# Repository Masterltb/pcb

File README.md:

# FreshVend — PCB điều khiển máy bán tô trái cây

**Rev-S3 là bản mẫu đang phát triển trên nhánh `fix/revs3-min-drill-0p3`.** Dùng ESP32-S3-WROOM-1U-N8, anten IPEX, USB-C dữ liệu và hai buck servo 6 V gá ngoài. RevB ở dưới là bản lịch sử; chưa bản nào được nghiệm thu sản xuất hàng loạt.

## Bàn giao Rev-S3

- [Bắt đầu tại đây: trạng thái, sơ đồ thư mục, bản hiện hành và backup](docs/rev_s3/handoff/README.md)
- [Project KiCad 10 Rev-S3](hardware/rev_s3/FV-CTRL_RevS3.kicad_pro)
- [Gerber 0,30 mm hiện hành cho 5 mẫu](releases/rev_s3/prototype-0p3-2026-10-29/FV-CTRL_RevS3-prototype-0p3-2026-10-29-Gerber.zip)
- [BOM nháp để kiểm tra linh kiện JLCPCB](assembly/rev_s3/draft/RevS3-JLCPCB-BOM-MATCHING-DRAFT.csv) và [CPL nháp](assembly/rev_s3/draft/RevS3-JLCPCB-CPL-MATCHING-DRAFT.csv)
- [ERC/DRC/parity hiện hành](reports/rev_s3/verified/RevS3-final-drc.json) và [rủi ro đặt hàng](docs/rev_s3/RevS3-JLCPCB-order-readiness-2026-10-29.md)

Các vị trí J4, J11/J12, J21 đang thiếu hàng ở báo giá JLCPCB; F2/F3 chưa có mã linh kiện. Gói Gerber dùng để kiểm tra/đặt mẫu PCB, chưa phải chứng nhận PCBA hoàn chỉnh.

## Bản RevB lưu để tham khảo

- [Project KiCad 10 RevB](hardware/revb/FV-CTRL_RevB.kicad_pro)
- [Trạng thái, kết quả kiểm tra và rủi ro cần duyệt](docs/revb/RevB-status.md)
- [ZIP review giữ nguyên thư mục](releases/revb/FV-CTRL_RevB-review.zip)
- [Gerber + drill mẫu RevB, 2026-10-26](releases/revb/FV-CTRL_RevB-Gerber-2026-10-26.zip)
- [Gói gửi xưởng báo giá/mẫu: Gerber, BOM, CPL và DFM](releases/revb/FV-CTRL_RevB-Prototype-Handoff-2026-10-26.zip)
- [Ghi chú lần xuất Gerber và giới hạn nghiệm thu](docs/revb/RevB-prototype-export-2026-10-26.md)
- [BOM linh kiện](docs/revb/bom/FV-CTRL_RevB-bom-review.csv)
- [Checklist cấp nguồn và chạy mẫu](docs/revb/RevB-review-and-bringup.md)
- [Mô phỏng Wokwi: ESP32, servo, IR và server local](simulation/revb/README.md)

Đọc [PROJECT.md](PROJECT.md) về yêu cầu và [AGENTS.md](AGENTS.md) trước khi sửa thiết kế. Không dùng các bản RevA/RevA2 để thay cho RevB.

## Cấu trúc

```text
hardware/
  rev_s3/               Project Rev-S3 đang phát triển; schematic, PCB và bảng thư viện
  revb/                 Project RevB lịch sử: mainboard, schematic và bảng thư viện
  reva2/                Bản cũ tham khảo: mainboard và IR RX
  archive/reva/         Nguồn RevA lịch sử, gồm các sửa đổi cục bộ chưa commit
libs/                   Thư viện dùng chung, giữ nguyên tên thư viện
cad/                    Cơ khí và mô phỏng FreeCAD
simulation/revb/        Mô phỏng chức năng Wokwi; không phải firmware production

docs/
  rev_s3/handoff/       Điểm vào bàn giao, đặt hàng và bring-up bản mẫu
  rev_s3/               Review, PDF schematic, STEP, pinout Rev-S3
  revb/
    bom/                BOM tổng, BOM SMT báo giá, linh kiện THT
    assembly/           Hình lắp ráp, ảnh 3D minh họa, tọa độ SMT, bản đồ via EP
    schematic/          Schematic xuất SVG/PNG để đọc
    RevB-status.md      Bắt đầu review tại đây
  reva2/                Tài liệu bản cũ
  archive/reva/         Tài liệu RevA lịch sử
  references/           Datasheet và hình tham khảo
  project/              Yêu cầu chung và ghi chú thử nghiệm
  mechanical/           Báo cáo cơ khí

reports/
  rev_s3/verified/      ERC, DRC/parity và netlist hiện hành
  rev_s3/work/          Log/checkpoint thử nghiệm cục bộ; không đưa vào Git
  revb/verified/        ERC/DRC, netlist và kết quả kiểm tra hiện hành
  revb/history/         Báo cáo trung gian đã lưu trong Git
  revb/work/            File chạy tạm/autoroute cục bộ, không đưa vào Git
  reva2/                Báo cáo RevA2
  archive/reva/         Báo cáo RevA lịch sử
  local/                Dữ liệu phân tích cục bộ, không đưa vào Git

releases/
  rev_s3/               Gerber hiện hành và các ZIP backup có ngày
  revb/                 ZIP review, Gerber/handoff mẫu có ngày và manifest SHA256
  archive/              ZIP/Gerber/handover các bản cũ; không dùng đặt RevB

tools/                  Công cụ; xem tools/README.md trước khi chạy
tests/                 Các bài kiểm tra generator RevA lịch sử
```

Các thư mục `hardware/<revision>` phải giữ quan hệ với `libs/`; không kéo riêng file project sang nơi khác. Trước khi đặt Rev-S3, đọc [bàn giao Rev-S3](docs/rev_s3/handoff/README.md) để phân biệt gói hiện hành với backup. Chưa có nghiệm thu phần cứng hoặc chấp thuận DFM của xưởng.

Xem [quy ước sắp xếp và kiểm tra](docs/repository-layout.md) để biết cách thêm file đúng chỗ.

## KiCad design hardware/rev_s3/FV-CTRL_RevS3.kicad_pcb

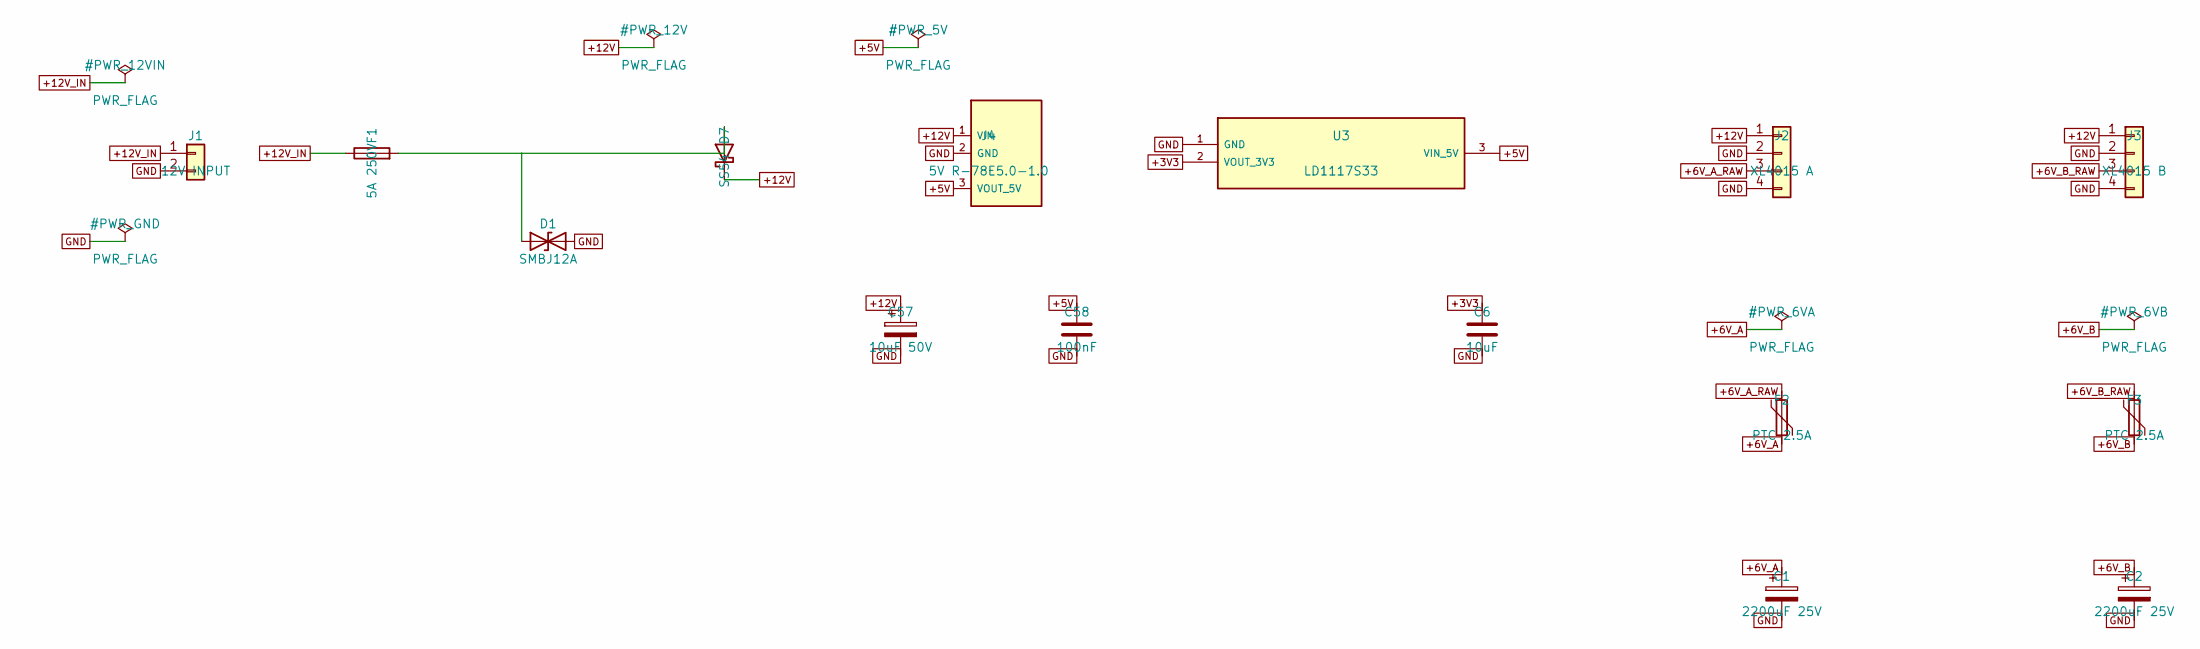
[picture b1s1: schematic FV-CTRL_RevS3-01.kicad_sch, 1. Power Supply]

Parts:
C1, C2: 2200uF 25V; CP_Radial_D12.5mm_P5.00mm
C6: 10uF; C_0603_1608Metric
C57: 10uF 50V; CP_Radial_D5.0mm_P2.00mm
C58: 100nF; C_0603_1608Metric
D1: SMBJ12A; D_SMB
D7: SS54; D_SMC
F1: 5A 250V; Fuseholder_Cylinder-5x20mm_Schurter_0031_8201_Horizontal_Op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
F2, F3: PTC 2.5A; Fuse_Bourns_MF-RHT300
J1: 12V INPUT; PhoenixContact_MSTBA_2,5_2-G-5,08_1x02_P5.08mm_Horizontal
J2: XL4015 A; PhoenixContact_MSTBA_2,5_4-G-5,08_1x04_P5.08mm_Horizontal
J3: XL4015 B; PhoenixContact_MSTBA_2,5_4-G-5,08_1x04_P5.08mm_Horizontal
J4: 5V R-78E5.0-1.0; RECOM_R78E5V1A
U3: LD1117S33; SOT-223-3_TabPin2

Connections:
+3V3: C6.1, U3.2 (VOUT_3V3); also elsewhere on the board
+6V_A_RAW: F2.1, J2.3
+6V_B_RAW: F3.1, J3.3
unnamed: D1.1 (A1), D7.2 (A), F1.2

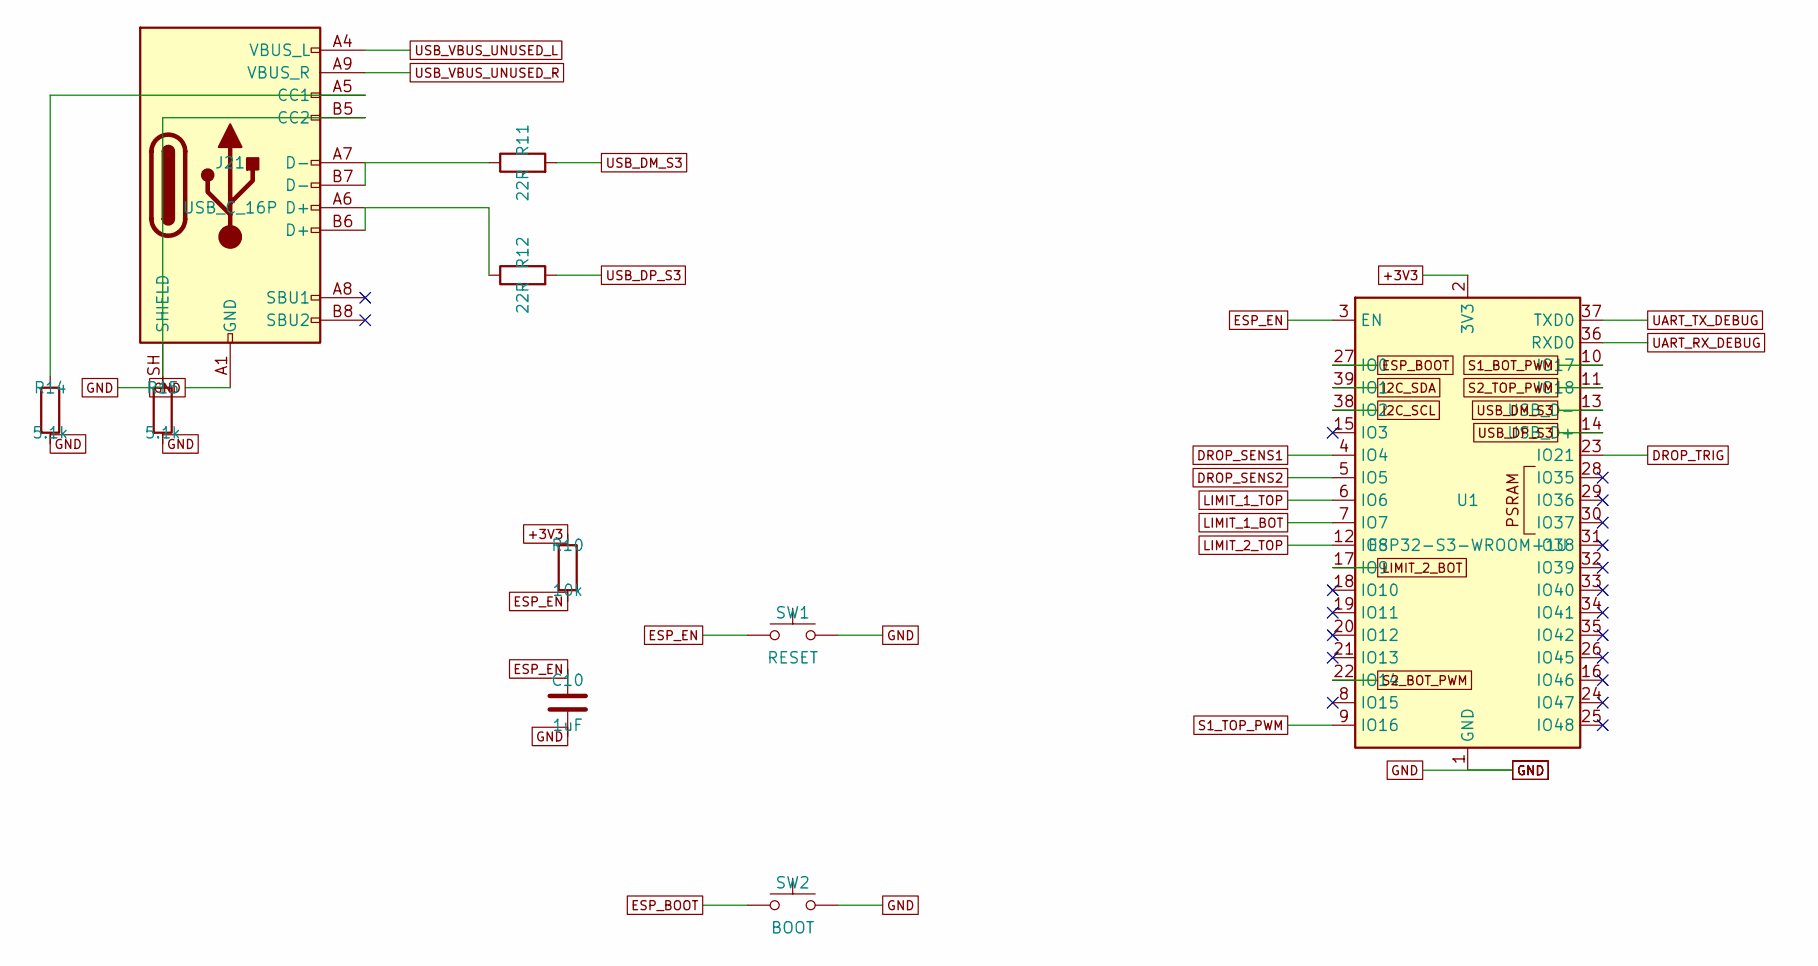
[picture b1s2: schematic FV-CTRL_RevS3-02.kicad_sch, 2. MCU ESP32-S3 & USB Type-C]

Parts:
C10: 1uF; C_0603_1608Metric
J21: USB_C_16P; USB_C_Receptacle_GCT_USB4105-xx-A_16P_TopMnt_Horizontal
R10: 10k; R_0603_1608Metric
R11, R12: 22R; R_0603_1608Metric
R14, R15: 5.1k; R_0603_1608Metric
SW1: RESET; SW_Push_SPST_NO_Alps_SKRK
SW2: BOOT; SW_Push_SPST_NO_Alps_SKRK
U1: ESP32-S3-WROOM-1U; ESP32-S3-WROOM-1U_0p3

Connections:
+3V3: R10.1, U1.2 (3V3); also elsewhere on the board
DROP_SENS1: U1.4 (IO4); also elsewhere on the board
DROP_SENS2: U1.5 (IO5); also elsewhere on the board
DROP_TRIG: U1.23 (IO21); also elsewhere on the board
ESP_BOOT: SW2.1, U1.27 (IO0)
ESP_EN: C10.1, R10.2, SW1.1, U1.3 (EN)
I2C_SCL: U1.38 (IO2); also elsewhere on the board
I2C_SDA: U1.39 (IO1); also elsewhere on the board
LIMIT_1_BOT: U1.7 (IO7); also elsewhere on the board
LIMIT_1_TOP: U1.6 (IO6); also elsewhere on the board
LIMIT_2_BOT: U1.17 (IO9); also elsewhere on the board
LIMIT_2_TOP: U1.12 (IO8); also elsewhere on the board
unnamed: J21.A5 (CC1), R14.1
unnamed: J21.B5 (CC2), R15.1
unnamed: J21.A6 (D+), J21.B6 (D+), R12.1
unnamed: J21.A7 (D-), J21.B7 (D-), R11.1
S1_BOT_PWM: U1.10 (IO17); also elsewhere on the board
S1_TOP_PWM: U1.9 (IO16); also elsewhere on the board
S2_BOT_PWM: U1.22 (IO14); also elsewhere on the board
S2_TOP_PWM: U1.11 (IO18); also elsewhere on the board
UART_RX_DEBUG: U1.36 (RXD0); also elsewhere on the board
UART_TX_DEBUG: U1.37 (TXD0); also elsewhere on the board
USB_DM_S3: R11.2, U1.13 (USB_D-)
USB_DP_S3: R12.2, U1.14 (USB_D+)
USB_VBUS_UNUSED_L: J21.A4 (VBUS_L), J21.B9 (VBUS_L)
USB_VBUS_UNUSED_R: J21.A9 (VBUS_R), J21.B4 (VBUS_R)

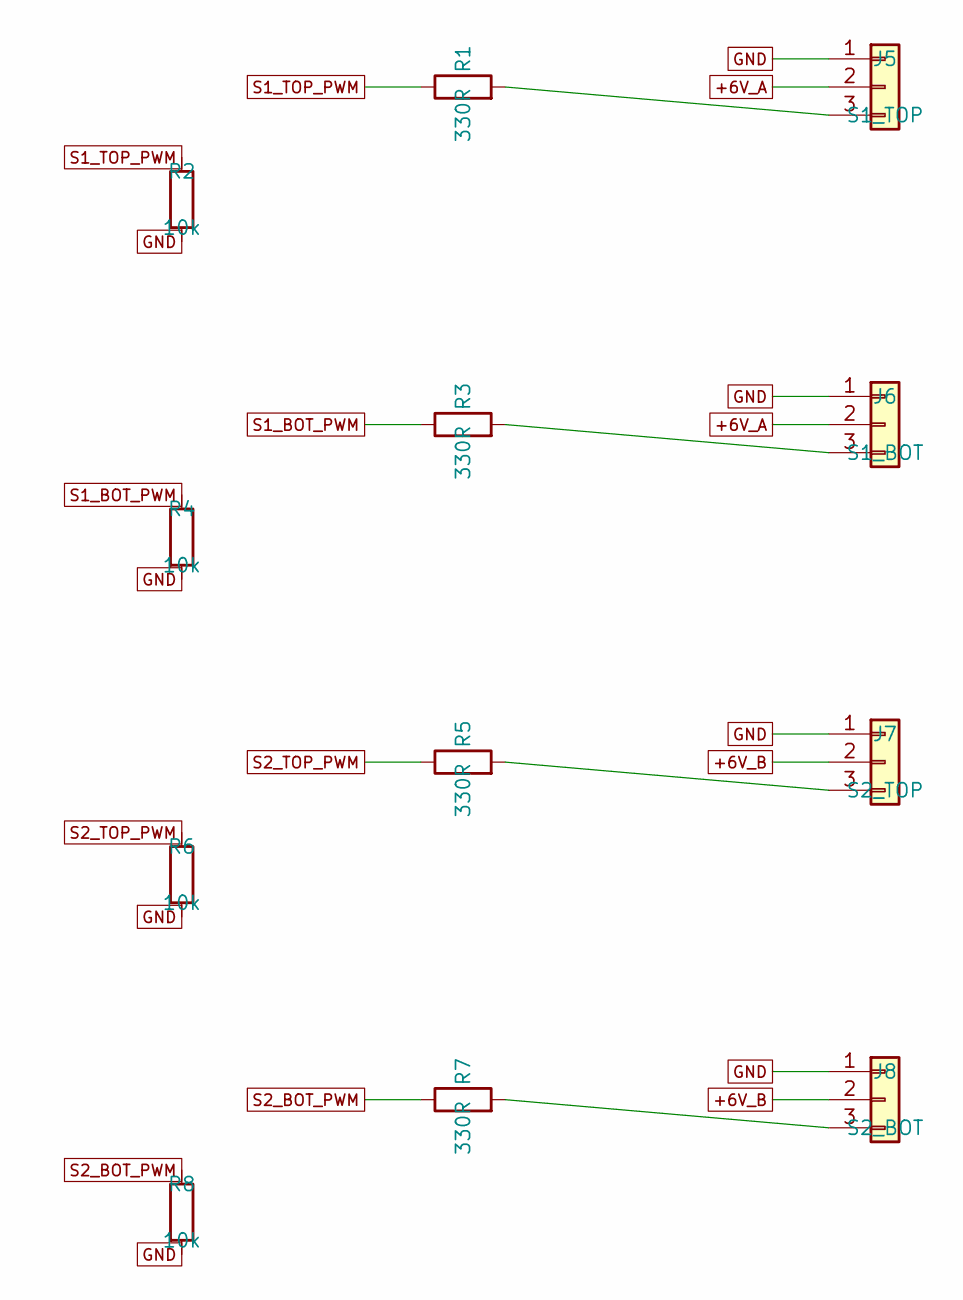
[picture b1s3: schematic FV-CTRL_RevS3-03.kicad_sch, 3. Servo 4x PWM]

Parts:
J5: S1_TOP; PinHeader_1x03_P2.54mm_Vertical
J6: S1_BOT; PinHeader_1x03_P2.54mm_Vertical
J7: S2_TOP; PinHeader_1x03_P2.54mm_Vertical
J8: S2_BOT; PinHeader_1x03_P2.54mm_Vertical
R1, R3, R5, R7: 330R; R_0603_1608Metric
R2, R4, R6, R8: 10k; R_0603_1608Metric

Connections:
unnamed: J5.3, R1.2
unnamed: J6.3, R3.2
unnamed: J7.3, R5.2
unnamed: J8.3, R7.2
S1_BOT_PWM: R3.1, R4.1; also elsewhere on the board
S1_TOP_PWM: R1.1, R2.1; also elsewhere on the board
S2_BOT_PWM: R7.1, R8.1; also elsewhere on the board
S2_TOP_PWM: R5.1, R6.1; also elsewhere on the board

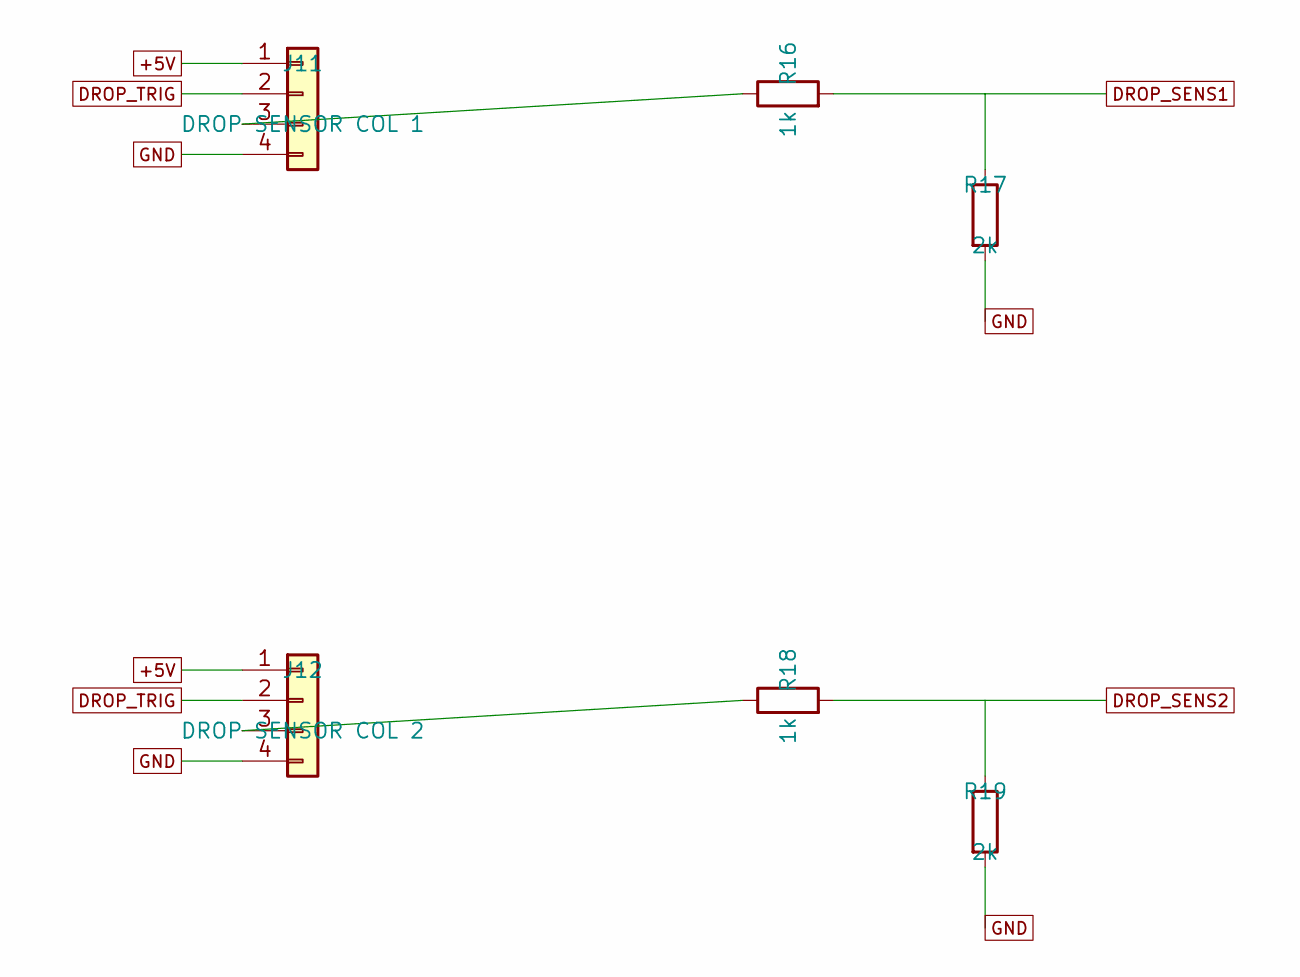
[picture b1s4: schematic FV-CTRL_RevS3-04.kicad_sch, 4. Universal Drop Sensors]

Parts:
J11: DROP SENSOR COL 1; JST_XH_B4B-XH-A_1x04_P2.50mm_Vertical
J12: DROP SENSOR COL 2; JST_XH_B4B-XH-A_1x04_P2.50mm_Vertical
R16, R18: 1k; R_0603_1608Metric
R17, R19: 2k; R_0603_1608Metric

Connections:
DROP_SENS1: R16.2, R17.1; also elsewhere on the board
DROP_SENS2: R18.2, R19.1; also elsewhere on the board
DROP_TRIG: J11.2, J12.2; also elsewhere on the board
unnamed: J11.3, R16.1
unnamed: J12.3, R18.1

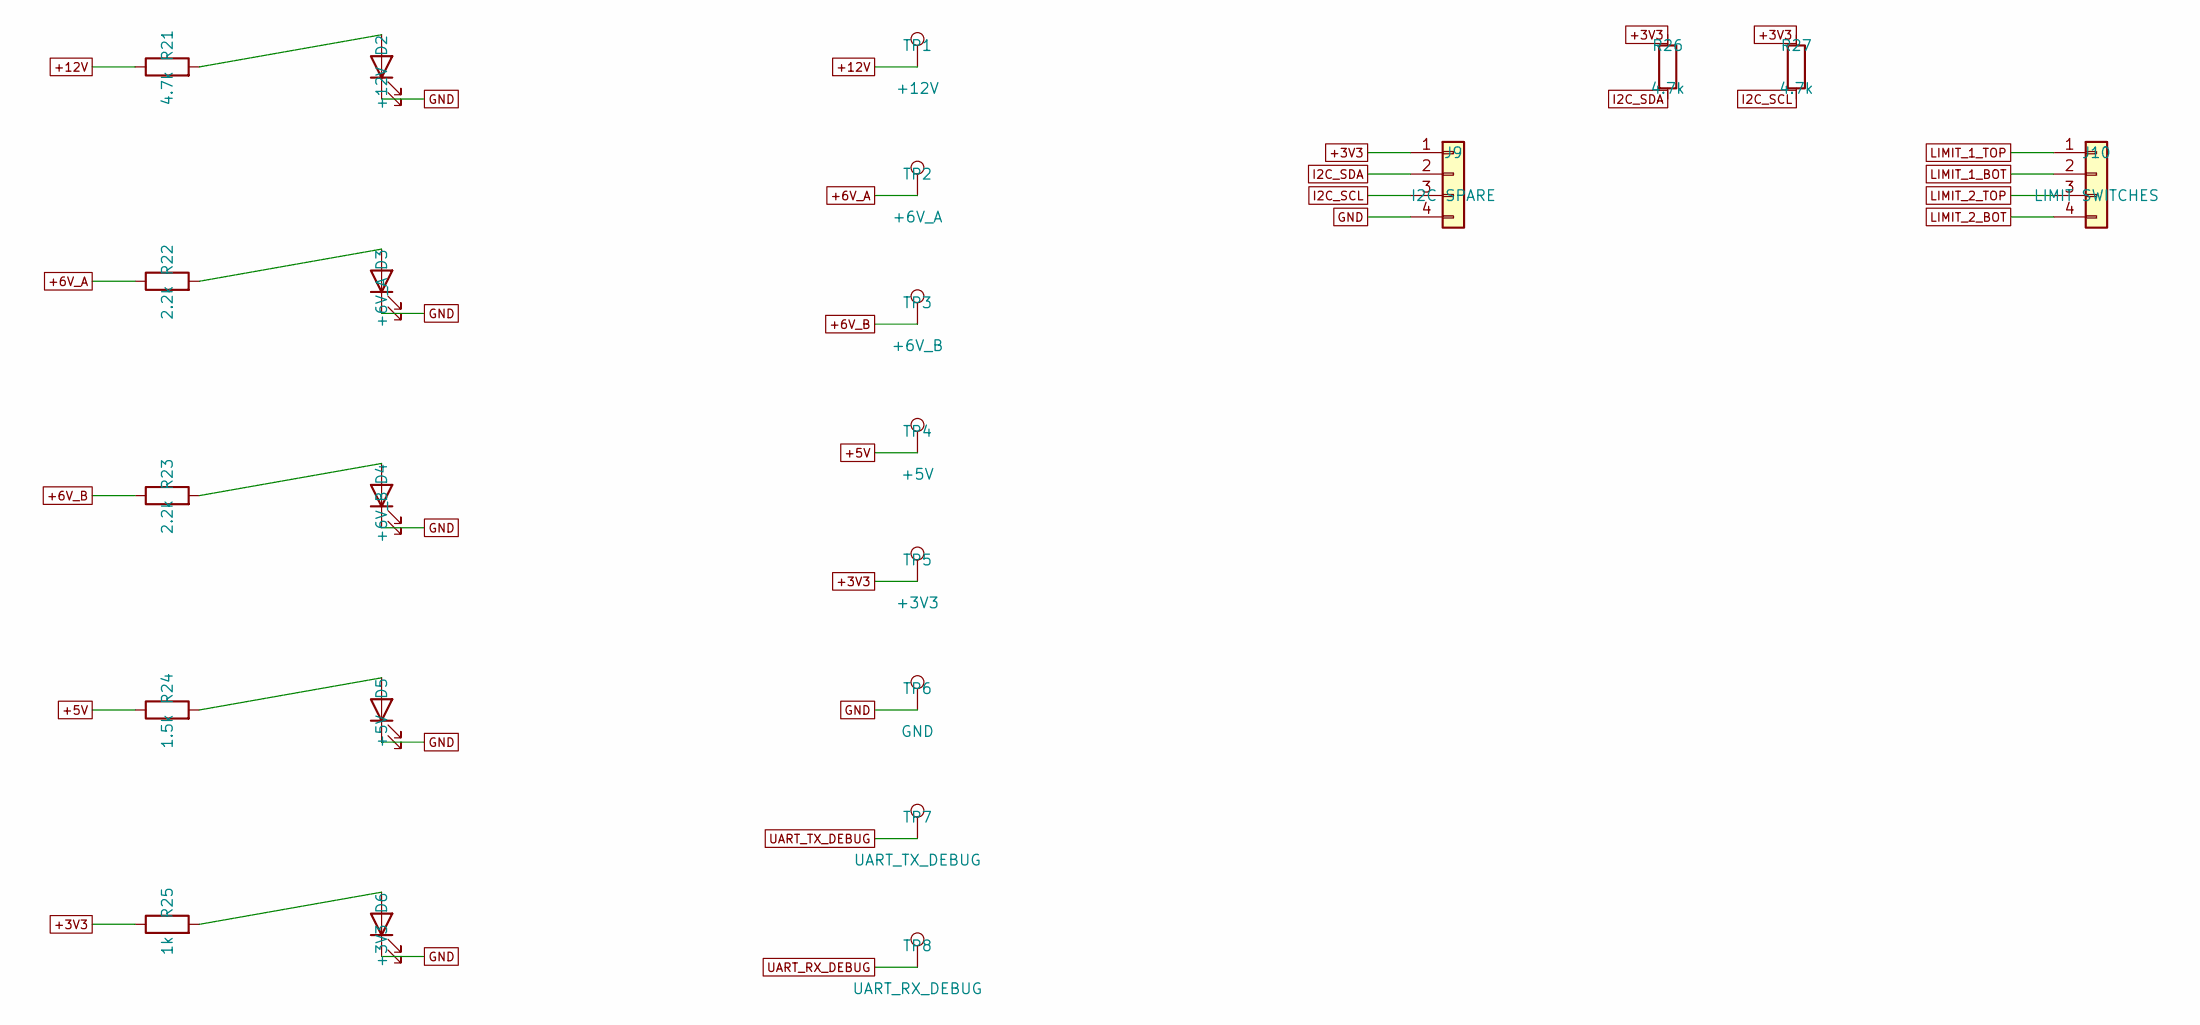
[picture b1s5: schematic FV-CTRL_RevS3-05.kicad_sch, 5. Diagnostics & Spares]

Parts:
D2: +12V; LED_0603_1608Metric
D3: +6V_A; LED_0603_1608Metric
D4: +6V_B; LED_0603_1608Metric
D5: +5V; LED_0603_1608Metric
D6: +3V3; LED_0603_1608Metric
J9: I2C SPARE; PinHeader_1x04_P2.54mm_Vertical
J10: LIMIT SWITCHES; PinHeader_1x04_P2.54mm_Vertical
R21, R26, R27: 4.7k; R_0603_1608Metric
R22, R23: 2.2k; R_0603_1608Metric
R24: 1.5k; R_0603_1608Metric
R25: 1k; R_0603_1608Metric
TP1: +12V; TestPoint_Pad_D1.5mm
TP2: +6V_A; TestPoint_Pad_D1.5mm
TP3: +6V_B; TestPoint_Pad_D1.5mm
TP4: +5V; TestPoint_Pad_D1.5mm
TP5: +3V3; TestPoint_Pad_D1.5mm
TP6: GND; TestPoint_Pad_D1.5mm
TP7: UART_TX_DEBUG; TestPoint_Pad_D1.5mm
TP8: UART_RX_DEBUG; TestPoint_Pad_D1.5mm

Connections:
+3V3: J9.1, R25.1, R26.1, R27.1, TP5.1; also elsewhere on the board
I2C_SCL: J9.3, R27.2; also elsewhere on the board
I2C_SDA: J9.2, R26.2; also elsewhere on the board
LIMIT_1_BOT: J10.2; also elsewhere on the board
LIMIT_1_TOP: J10.1; also elsewhere on the board
LIMIT_2_BOT: J10.4; also elsewhere on the board
LIMIT_2_TOP: J10.3; also elsewhere on the board
unnamed: D2.2 (A), R21.2
unnamed: D3.2 (A), R22.2
unnamed: D4.2 (A), R23.2
unnamed: D5.2 (A), R24.2
unnamed: D6.2 (A), R25.2
UART_RX_DEBUG: TP8.1; also elsewhere on the board
UART_TX_DEBUG: TP7.1; also elsewhere on the board

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
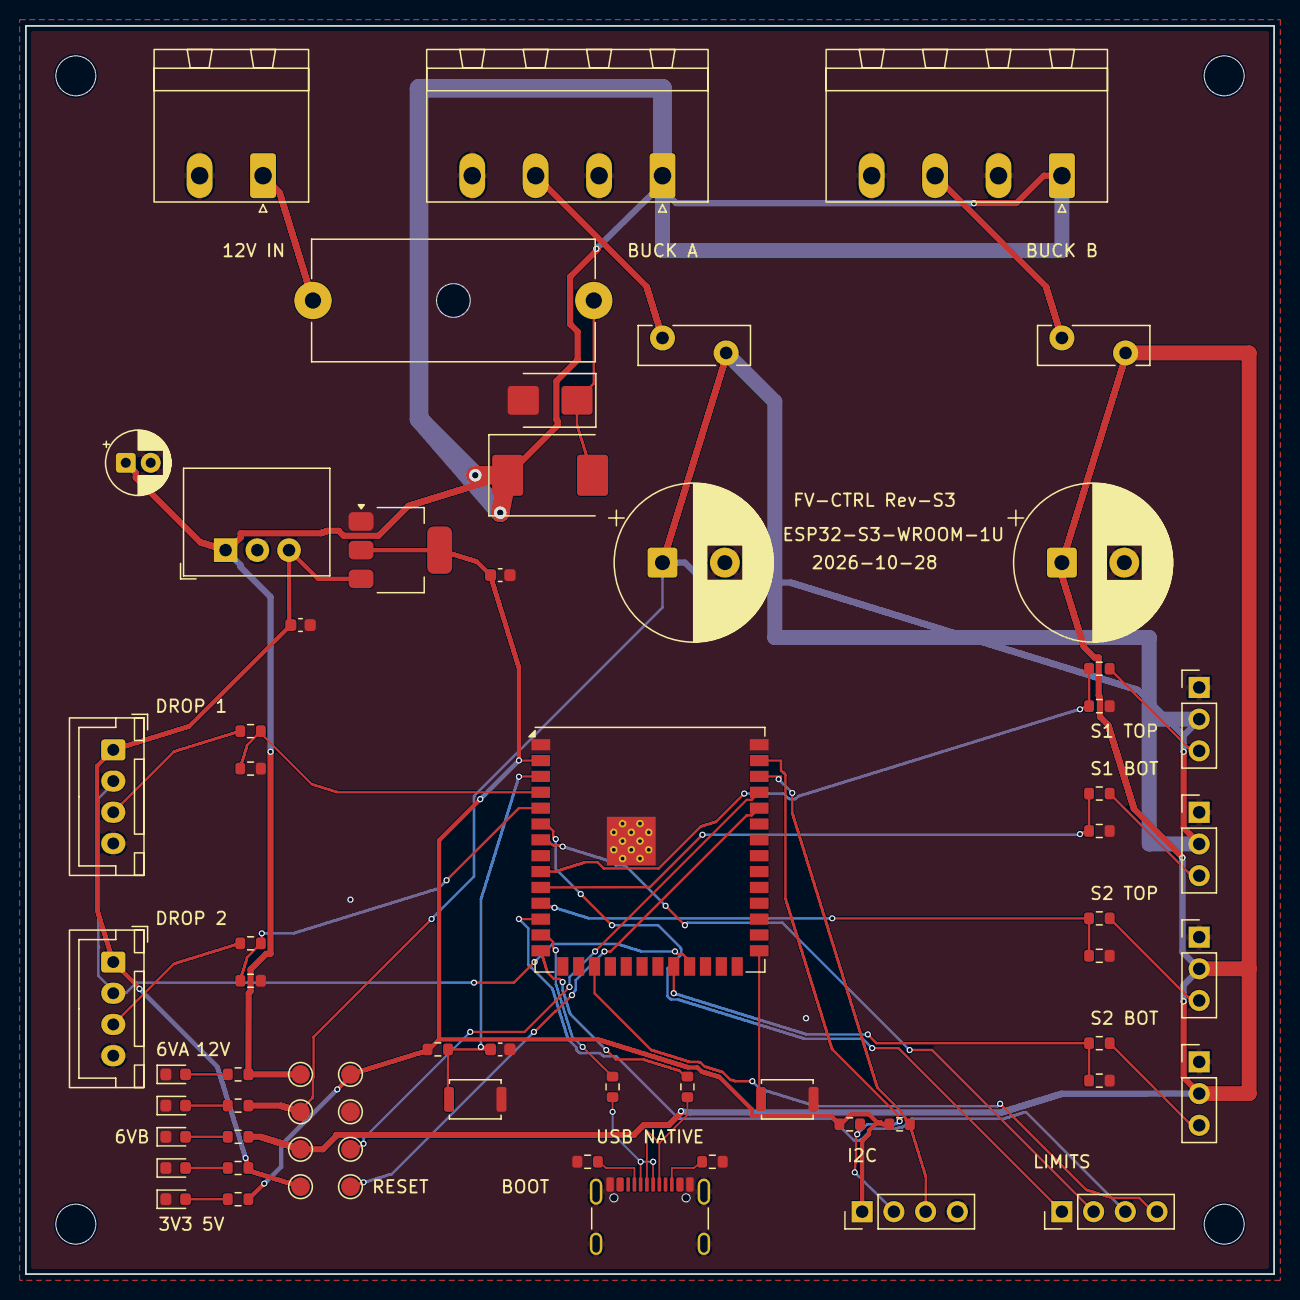
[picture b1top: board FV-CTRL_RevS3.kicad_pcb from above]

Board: 2 copper layers, 100.0 x 100.0 mm, 69 parts (0 on the bottom side), 46 nets.

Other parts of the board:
H1, H2, H3, H4: MountingHole_3.2mm_M3
